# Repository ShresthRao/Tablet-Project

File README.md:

# Tablet Project
## Description
This project is a custom tablet. It contains a custom PCB and case. The PCB connects to a CM4 Lite Wireless module for processing and wireless connections. The PCB is connected to a Viekk VK1200 V2 device that is used as the digitiser, stylus and the display.

## Bill of Materials (BOM)

* Note: All prices are in USD (inclusive of GST where applicable). Production and assembly files contain additional specs where applicable.
* Note: Bom for Item 4: JLCPCB Custom Manufactured PCB is in /Production/assembly/Custom Tablet_bom_raw.csv, /Production/assembly/Custom Tablet_jlcpcb_bom.csv

### Purchased Components

| Item | Qty | Component | Price/1 Item (USD) | Link | Description |
| :---: | :---: | :--- | :---: | :--- | :--- |
| 1 | 2 | NOVA 9060100 8000mAh 3.7V Micro LiPo Battery Pack with PCB & 100mm Cable | $9.34 | [Robu.in](https://robu.in/product/nova-9060100-8000mah-3-7v-lipo-battery-pack/) | Lined in Parallel |
| 2 | 4 | Harwin R25-1001102 Hex Standoffs | $0.51 | [Element14](https://in.element14.com/harwin/r25-1001102/standoff-hex-f-f-brass-m2-5-11mm/dp/3754478) | Standoffs for CM4 module |
| 3 | 1 | Raspberry Pi Compute Module 4 | $110.16 | [Element14](https://in.element14.com/raspberry-pi/cm4104000/rpi-compute-module-4-lite-4gb/dp/3563487) | Compute module |
| 4 | 1 | JLCPCB Custom Manufactured PCB | $279.95 | [JLCPCB](https://cart.jlcpcb.com/quote?spm=jlcpcb.Public.2006&jlc_vid=TlcPUgdeEgRZAlRTTlRaVAFVFlRZV1IFRFgLAQdVRFIxVlNeQVBYVlxURlZbVDsOAxUeFF5JWAsCBBQFFU8NCAlJ) | Custom PCB Ordered through JLCPCB |
| 5 | 1 | VEIKK VK1200 V2 Drawing Tablet | $157.65 | [Amazon](https://www.amazon.in/gp/product/B08G8CKSWK/) | Acts as the Screen, Digitiser and Stylus |
| 6 | 1 | Heat Shrink Tubing Kit (328 pcs) | $1.64 | [Robu.in](https://robu.in/product/328pcs-heat-shrink-tube-heat-shrink-tube-kit/) | Protection against short circuits |
| 7 | 1 | High-Temperature Kapton Polyimide Tape (10mm × 33m) | $1.03 | [Robu.in](https://robu.in/product/10mm-33m-100ft-high-temperature-heat-resistant-polyimide-kapton-tape-hot/) | Insulation |
| 8 | 1 | Digital Multimeter (Small LCD, AC/DC) | $1.80 | [Robu.in](https://robu.in/product/digital-multimeter-small-yellow-color-lcd-ac-dc-measuring-voltage-current/) | Tool to check for battery voltage and proper functionality |
| 9 | 1 | Multimeter Test Probes | $1.25 | [Robu.in](https://robu.in/product/1-month-warranty-1260/) | Probes for multimeter |
| Total | | | $575 (Adjusted for future price changes) | | |

### On-Hand Hardware & Tools

* Storage: Micro-SD card (64GB+)
* Cables: 3x USB-C cables, 1x Short HDMI cable
* Wiring: Red and Black battery wire
* Tools & Consumables: Soldering iron, flux, solder, tweezers, superglue
* Peripherals: USB keyboard and mouse

## Specifications
### Screen:
11.6 inch
Laminated anti-glare
8,192 levels of pressure sensitivity
Resolution is 1920 × 1080 pixels (Full HD)
Color Gamut: 72% NTSC

### PCB
1 HDMI port for connection of VIEKK VK1200 V2 device.
1 SD card slot
2 USB-C ports
2 Connectors for CM4 Lite Wireless module
1 Solder pads for connection of batteries

### Stylus
2 battery-less styluses
8,192 levels of pressure
60 degrees of tilt
290 RPS of report rate
5080 LPI of resolution

### Case (total size of custom tablet)
202 mm width
378 mm length
24 mm tall

### Software
Raspberry Pi OS (64-bit) with VIEKK drivers

## Screenshots of the design:
### Schematic
#### Full Screenshot

#### Part-Wise screenshots

### PCB
#### Zoned

#### Un-Zoned

### CAD
#### Assembly

#### Bottom Case

#### Top Case

****

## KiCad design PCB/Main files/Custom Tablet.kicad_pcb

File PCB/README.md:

# PCB Files
These are the files that are used to make your own changes to the PCB.
They are files for personal use, not for production

## Main files
Base files to open in KiCad

## Custom Libraries and 3D models
Files to import into KiCad as Footrprints and Symbols for specific parts of the PCB.

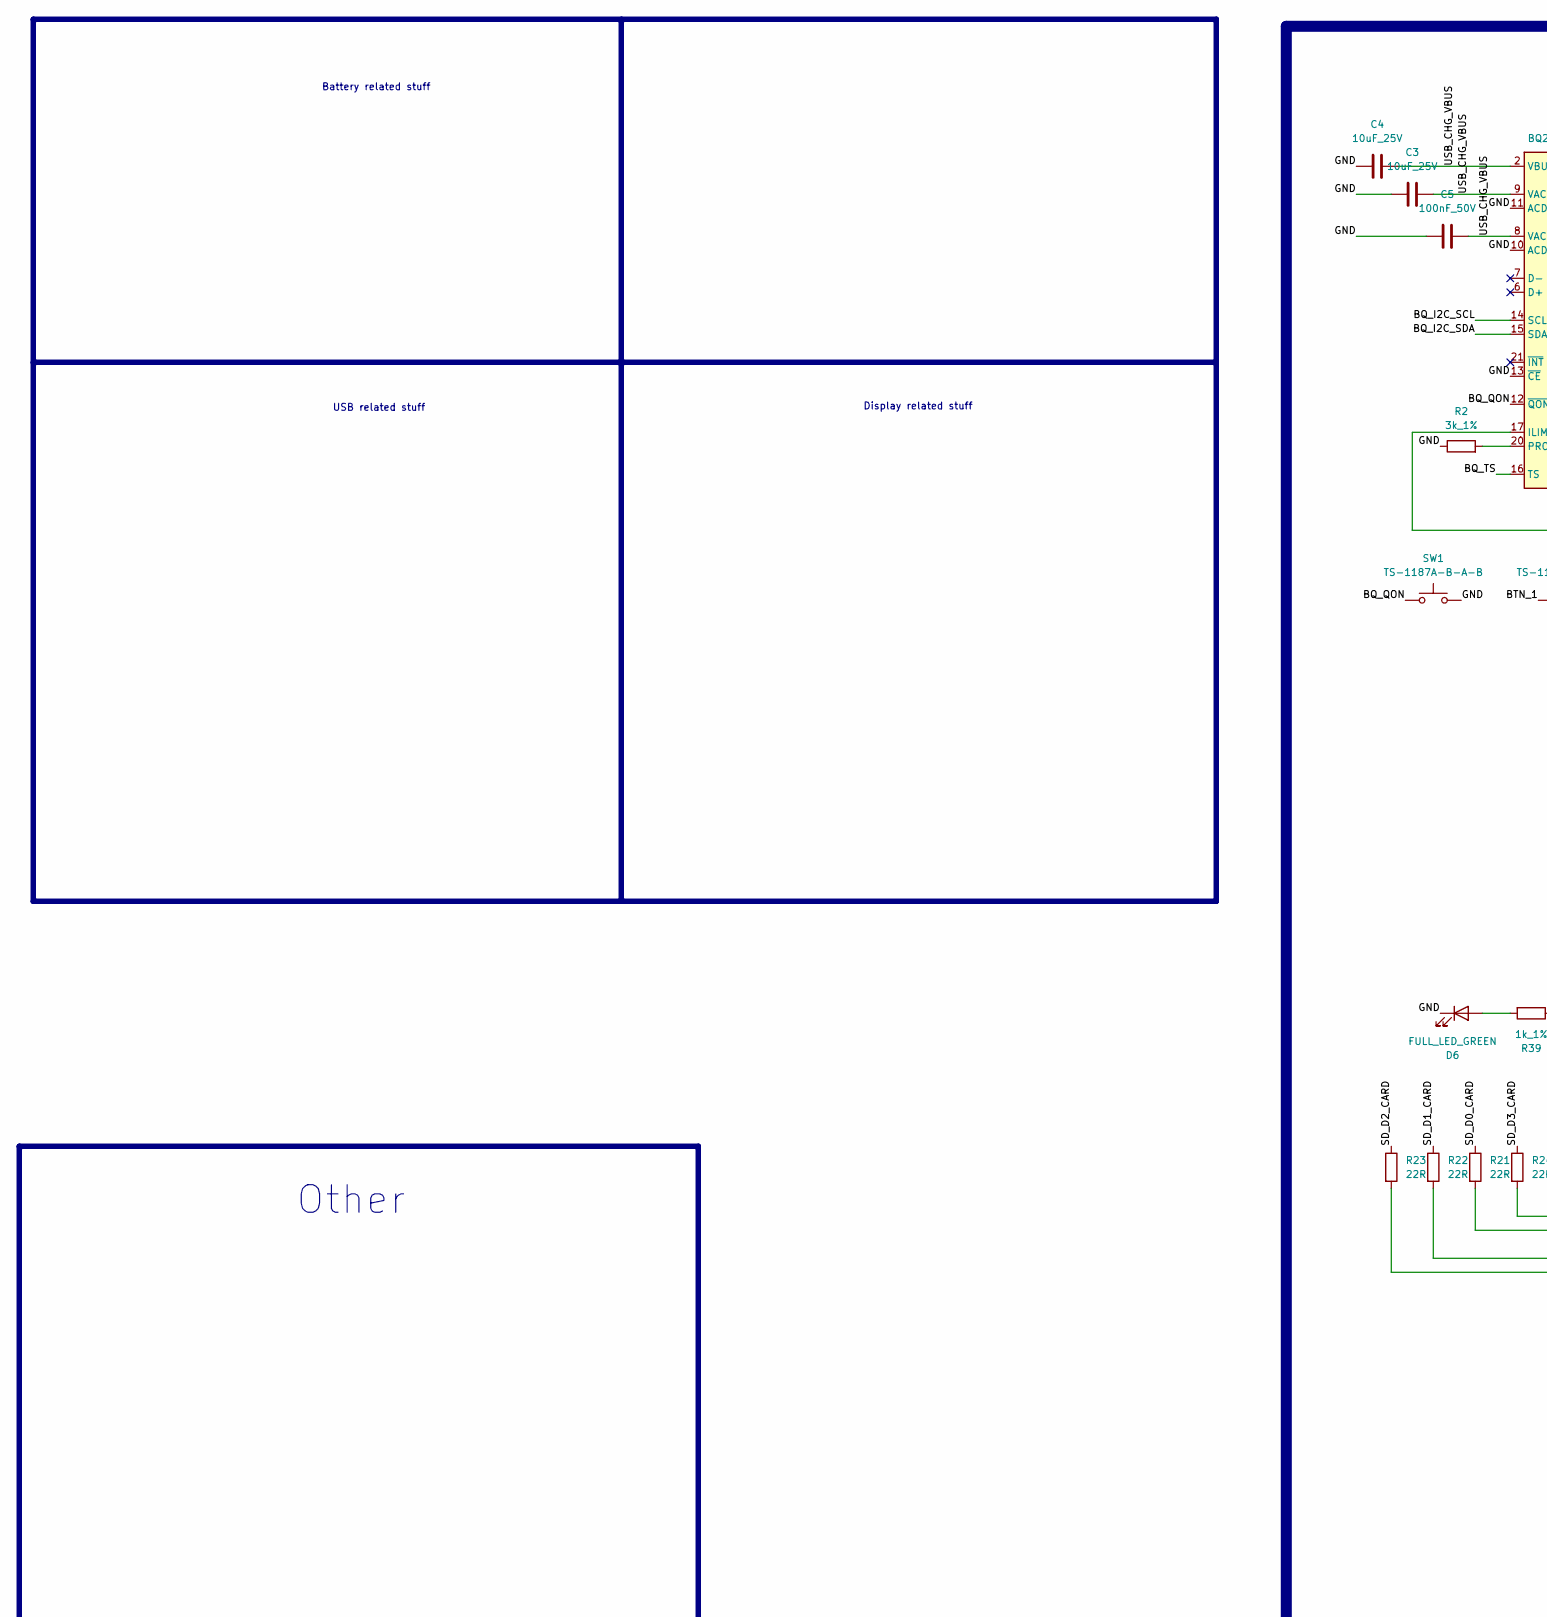
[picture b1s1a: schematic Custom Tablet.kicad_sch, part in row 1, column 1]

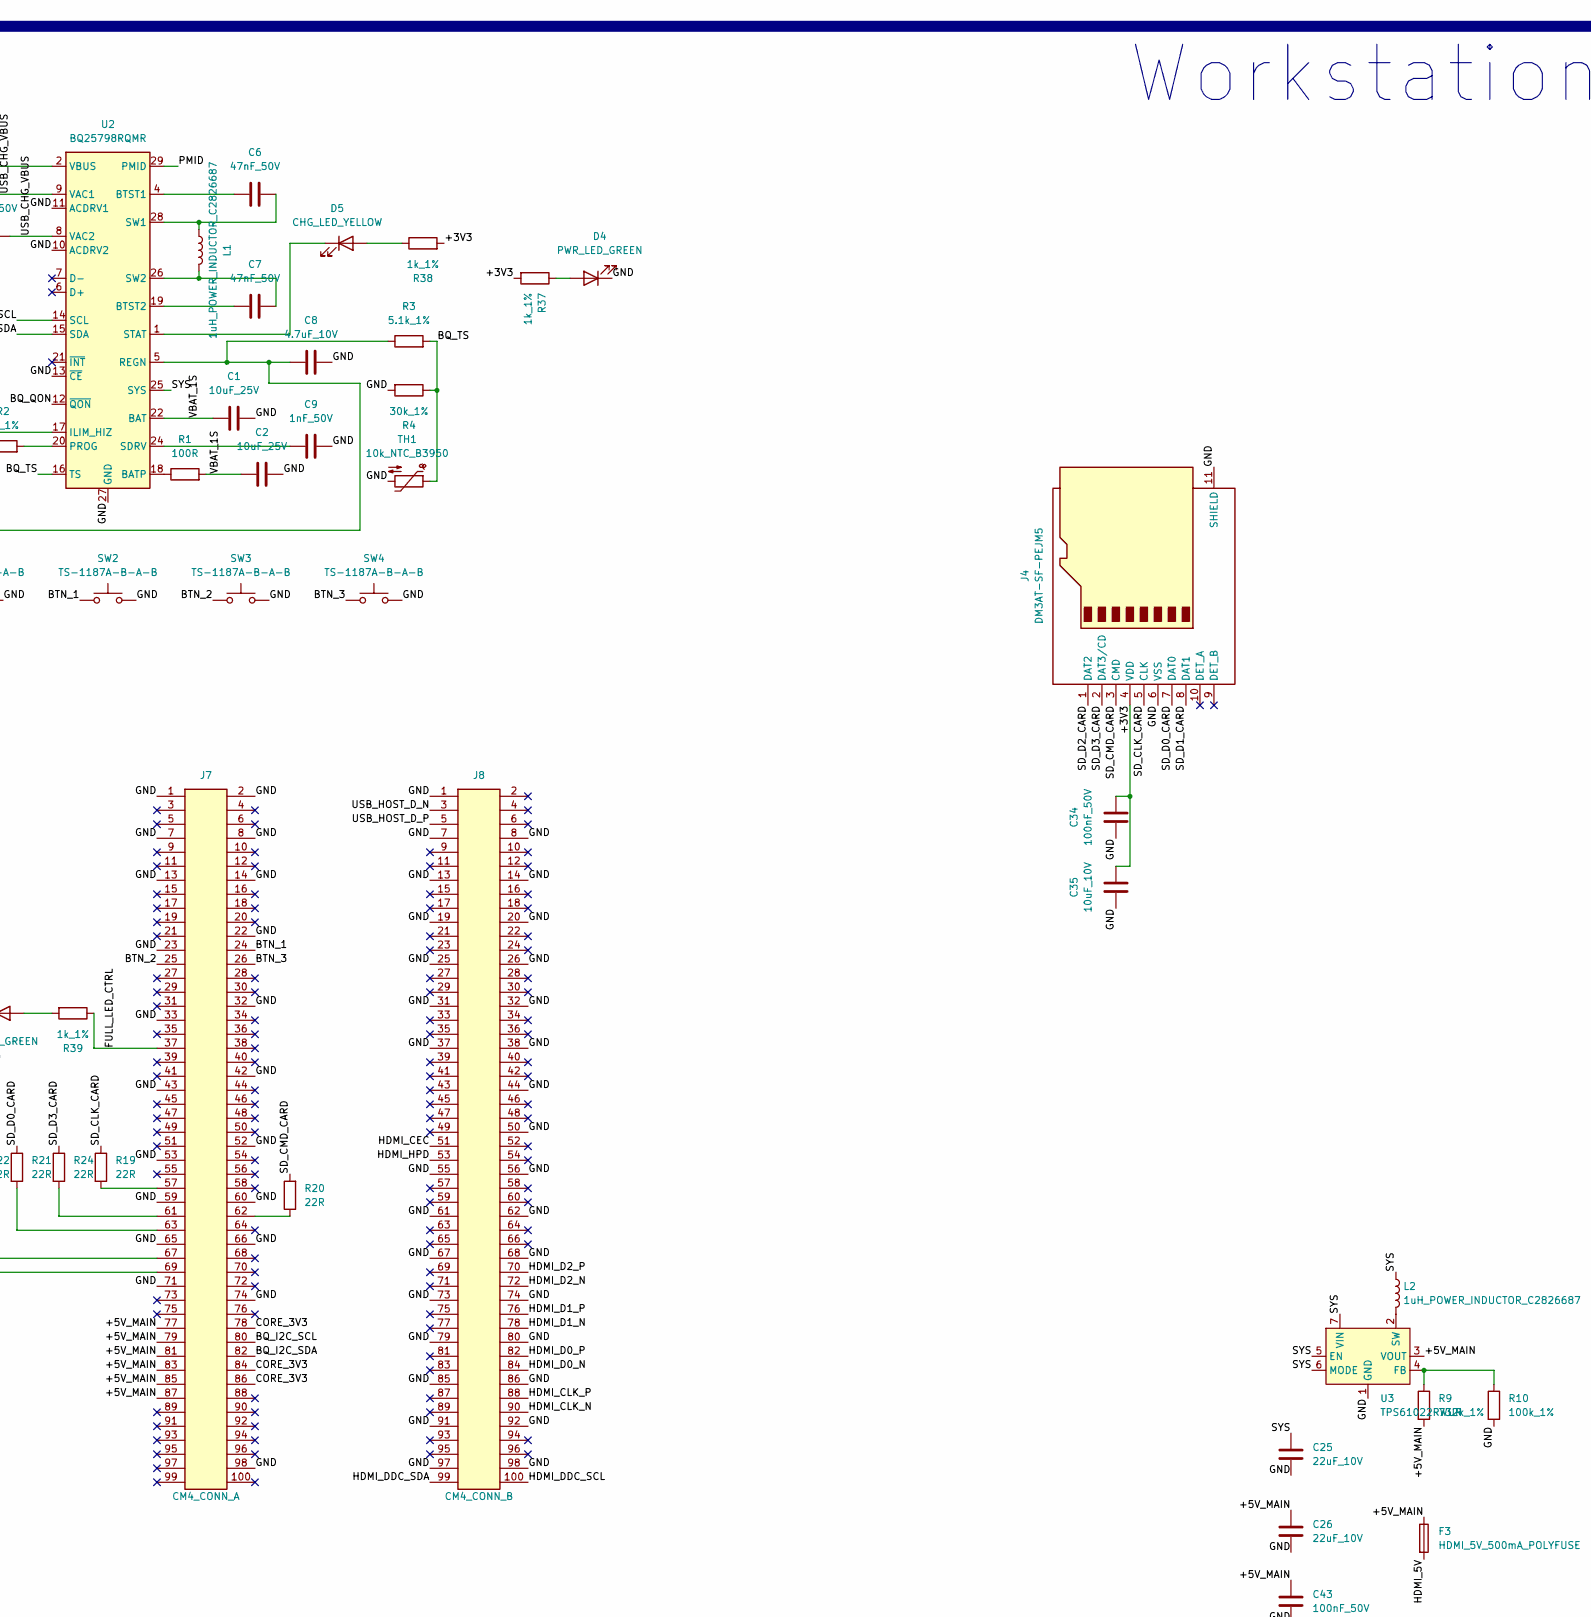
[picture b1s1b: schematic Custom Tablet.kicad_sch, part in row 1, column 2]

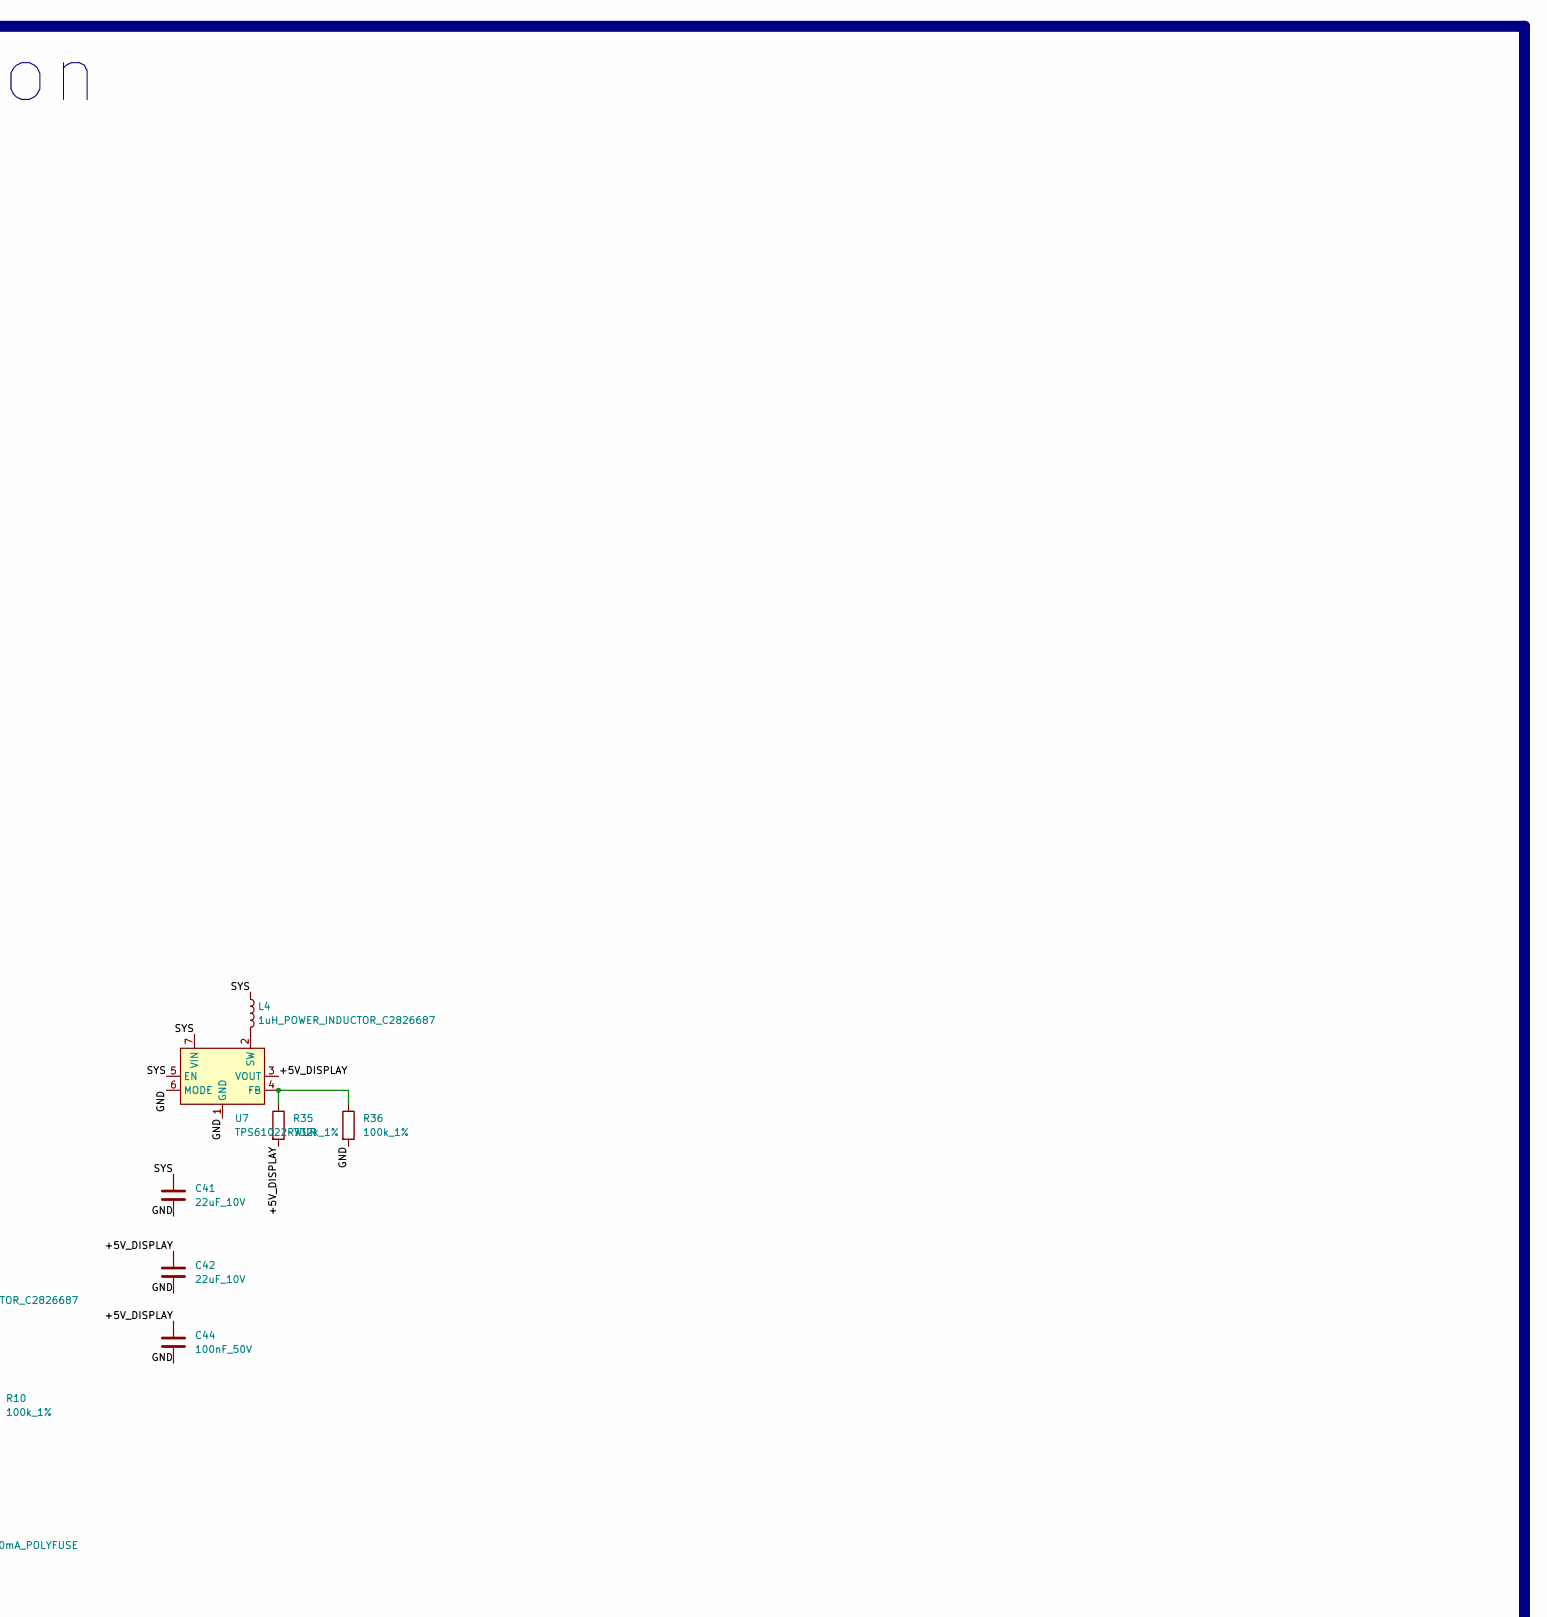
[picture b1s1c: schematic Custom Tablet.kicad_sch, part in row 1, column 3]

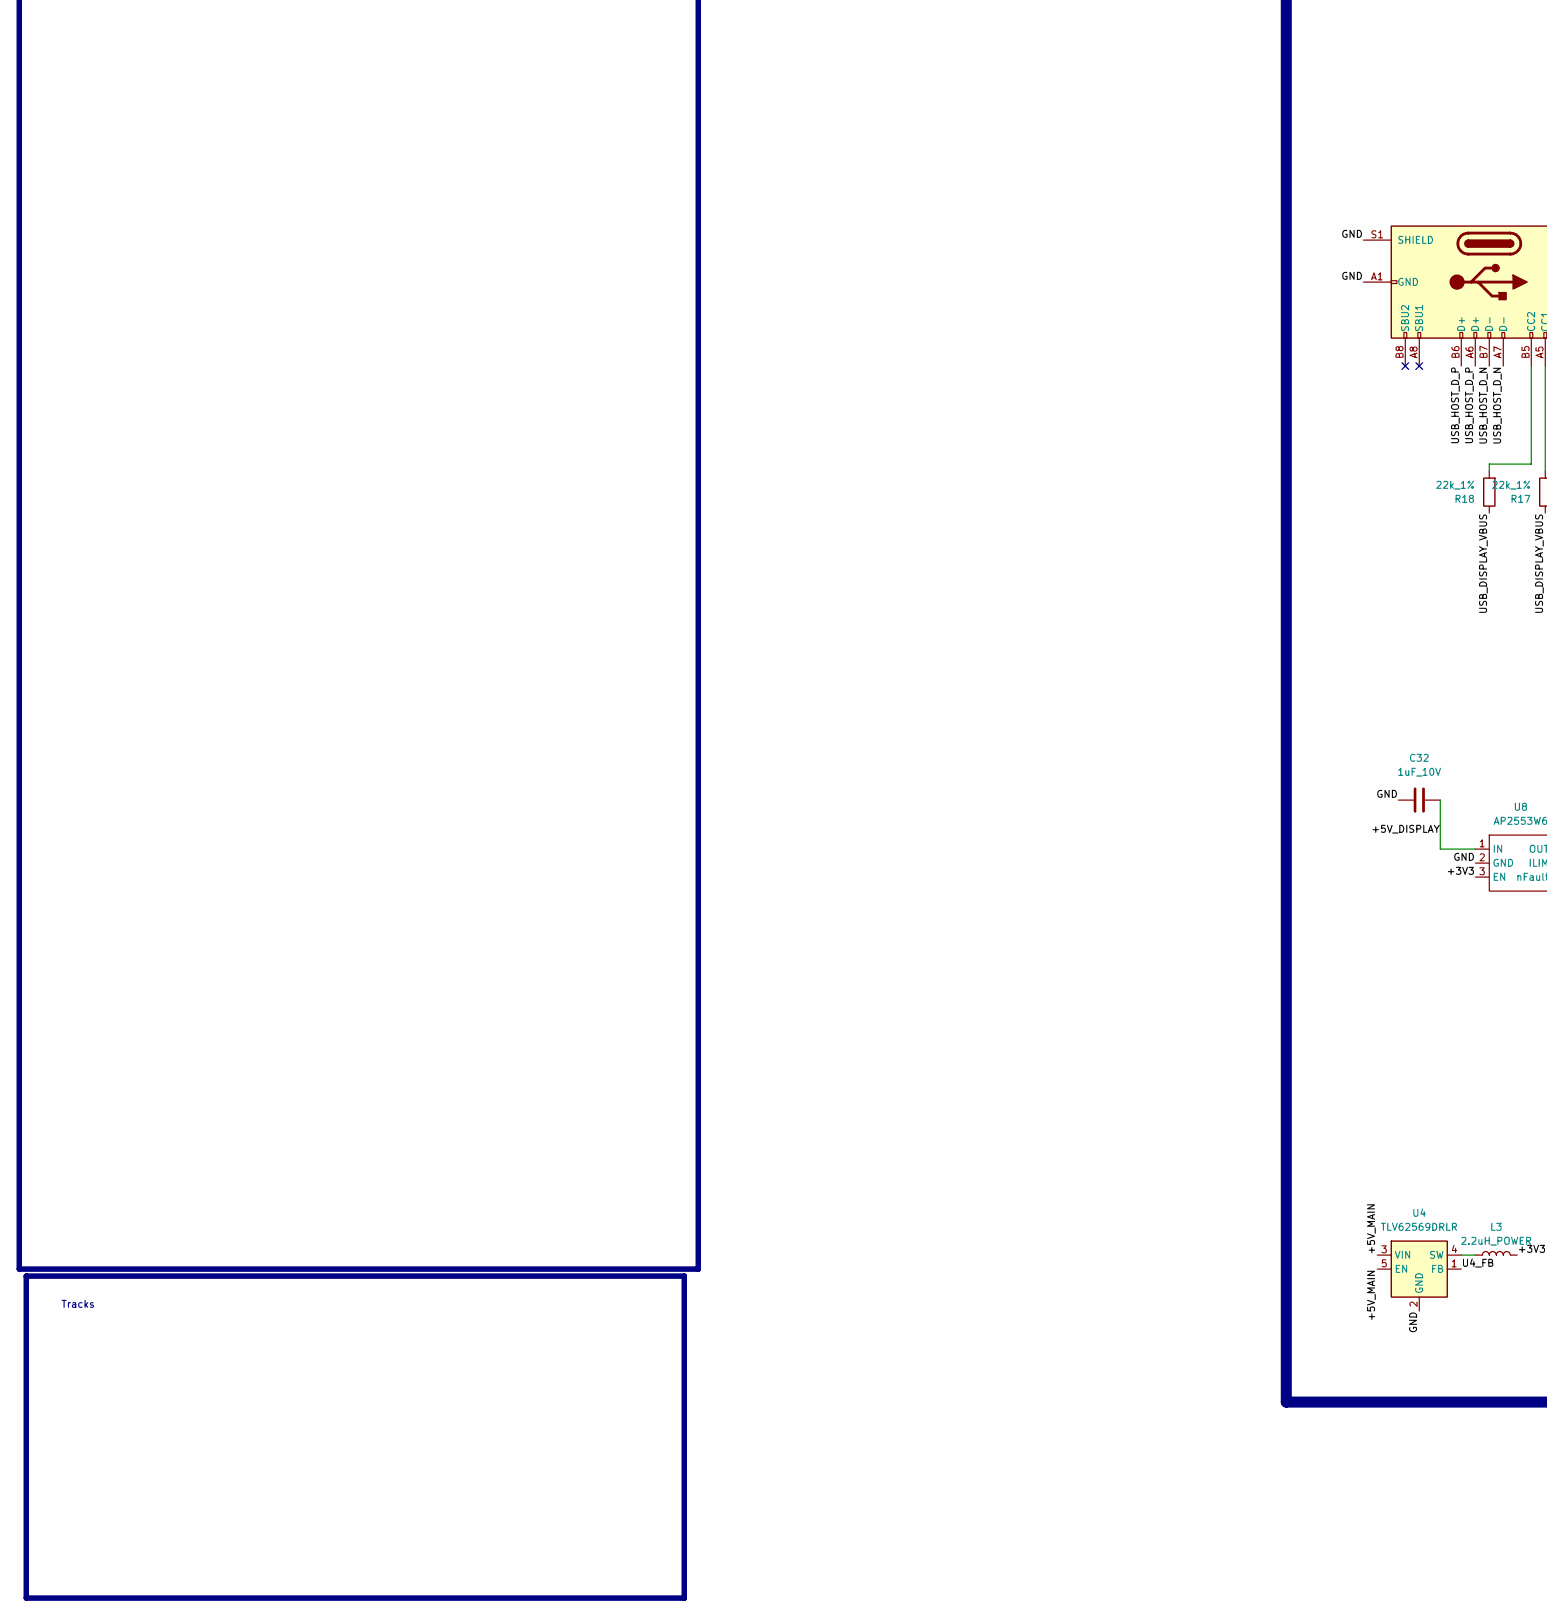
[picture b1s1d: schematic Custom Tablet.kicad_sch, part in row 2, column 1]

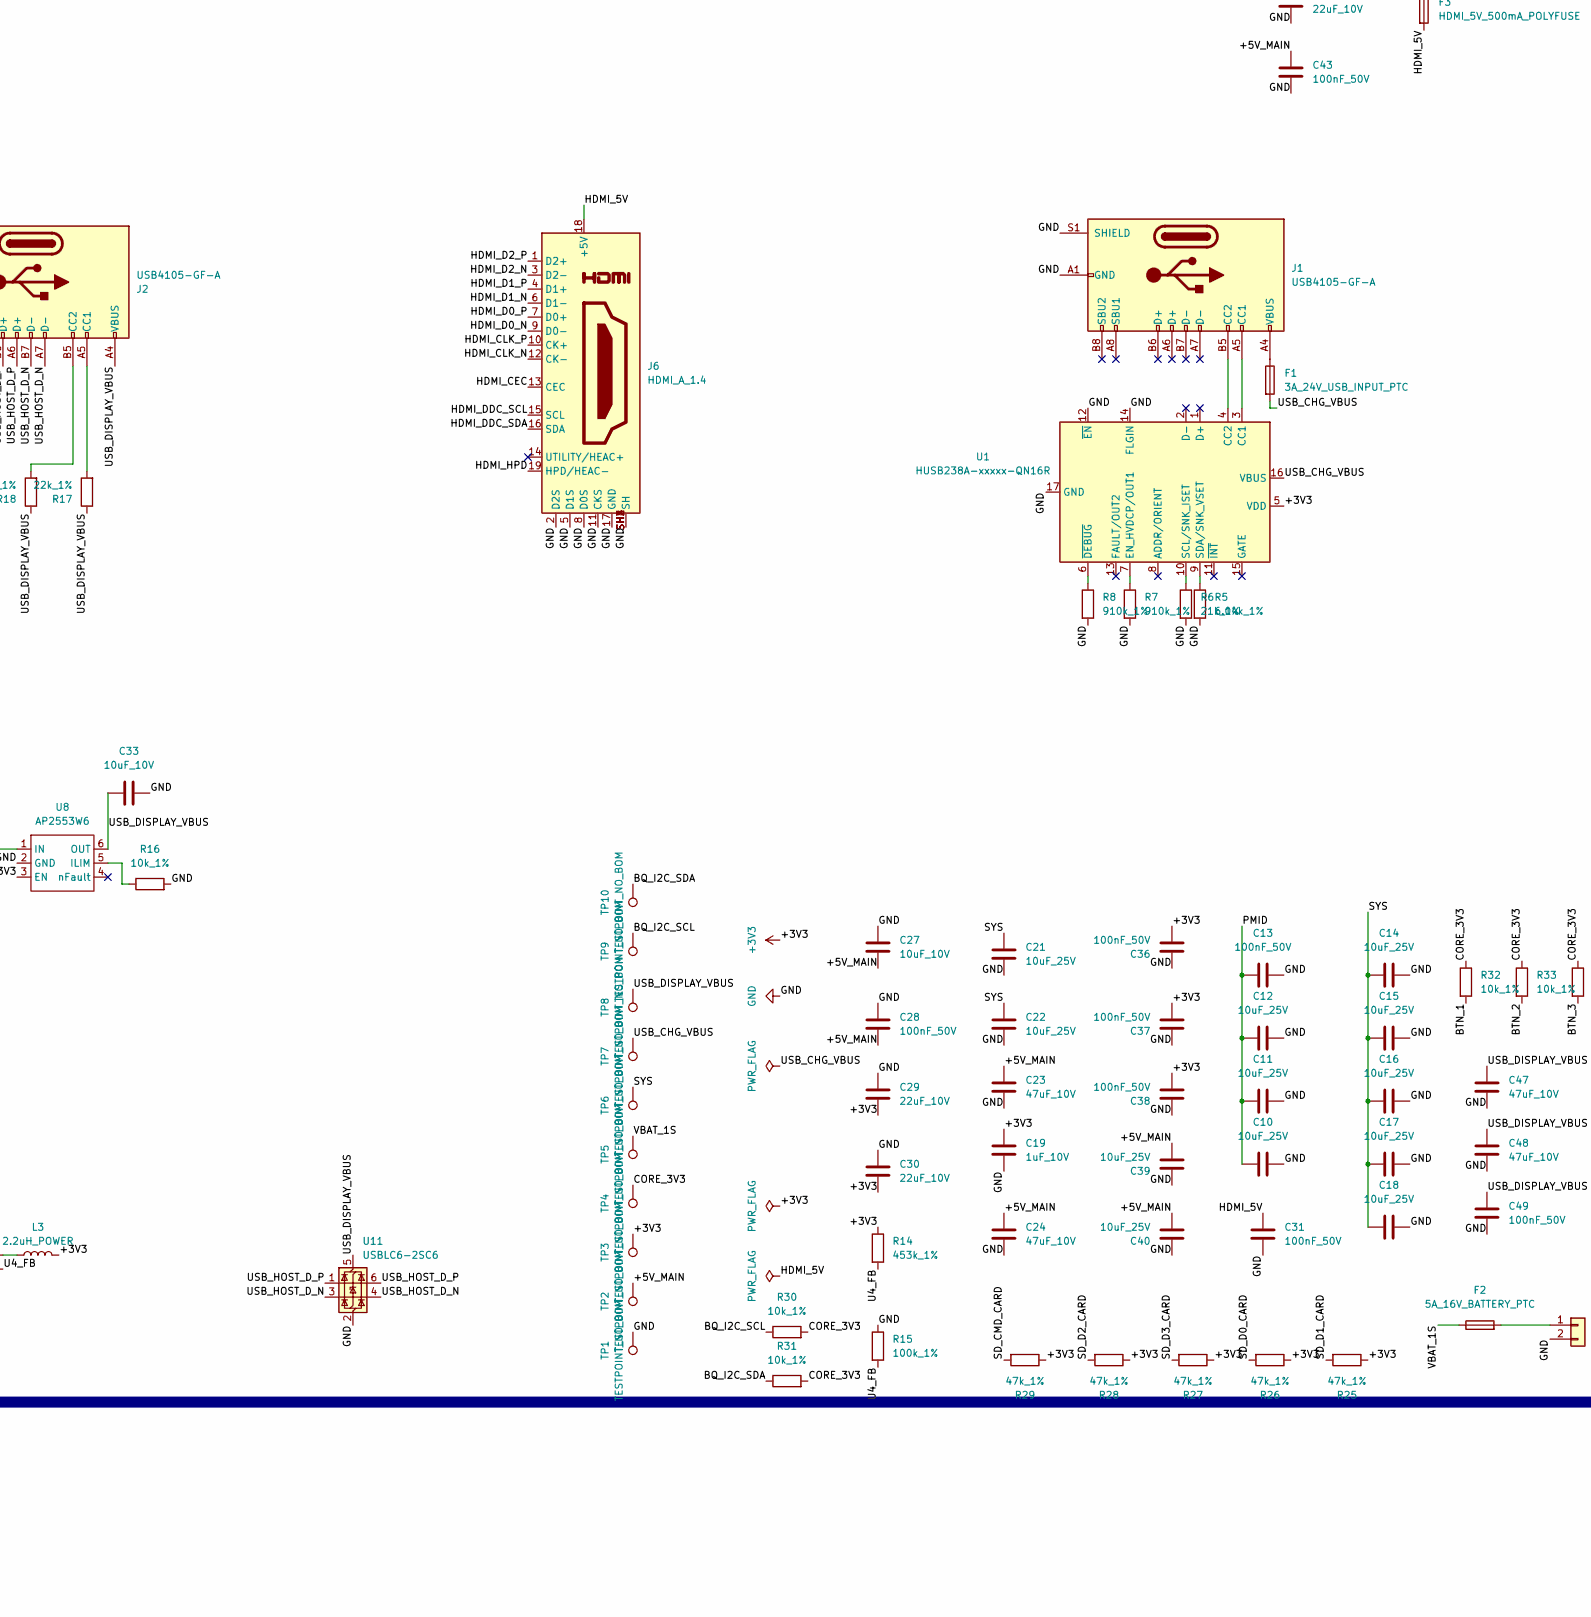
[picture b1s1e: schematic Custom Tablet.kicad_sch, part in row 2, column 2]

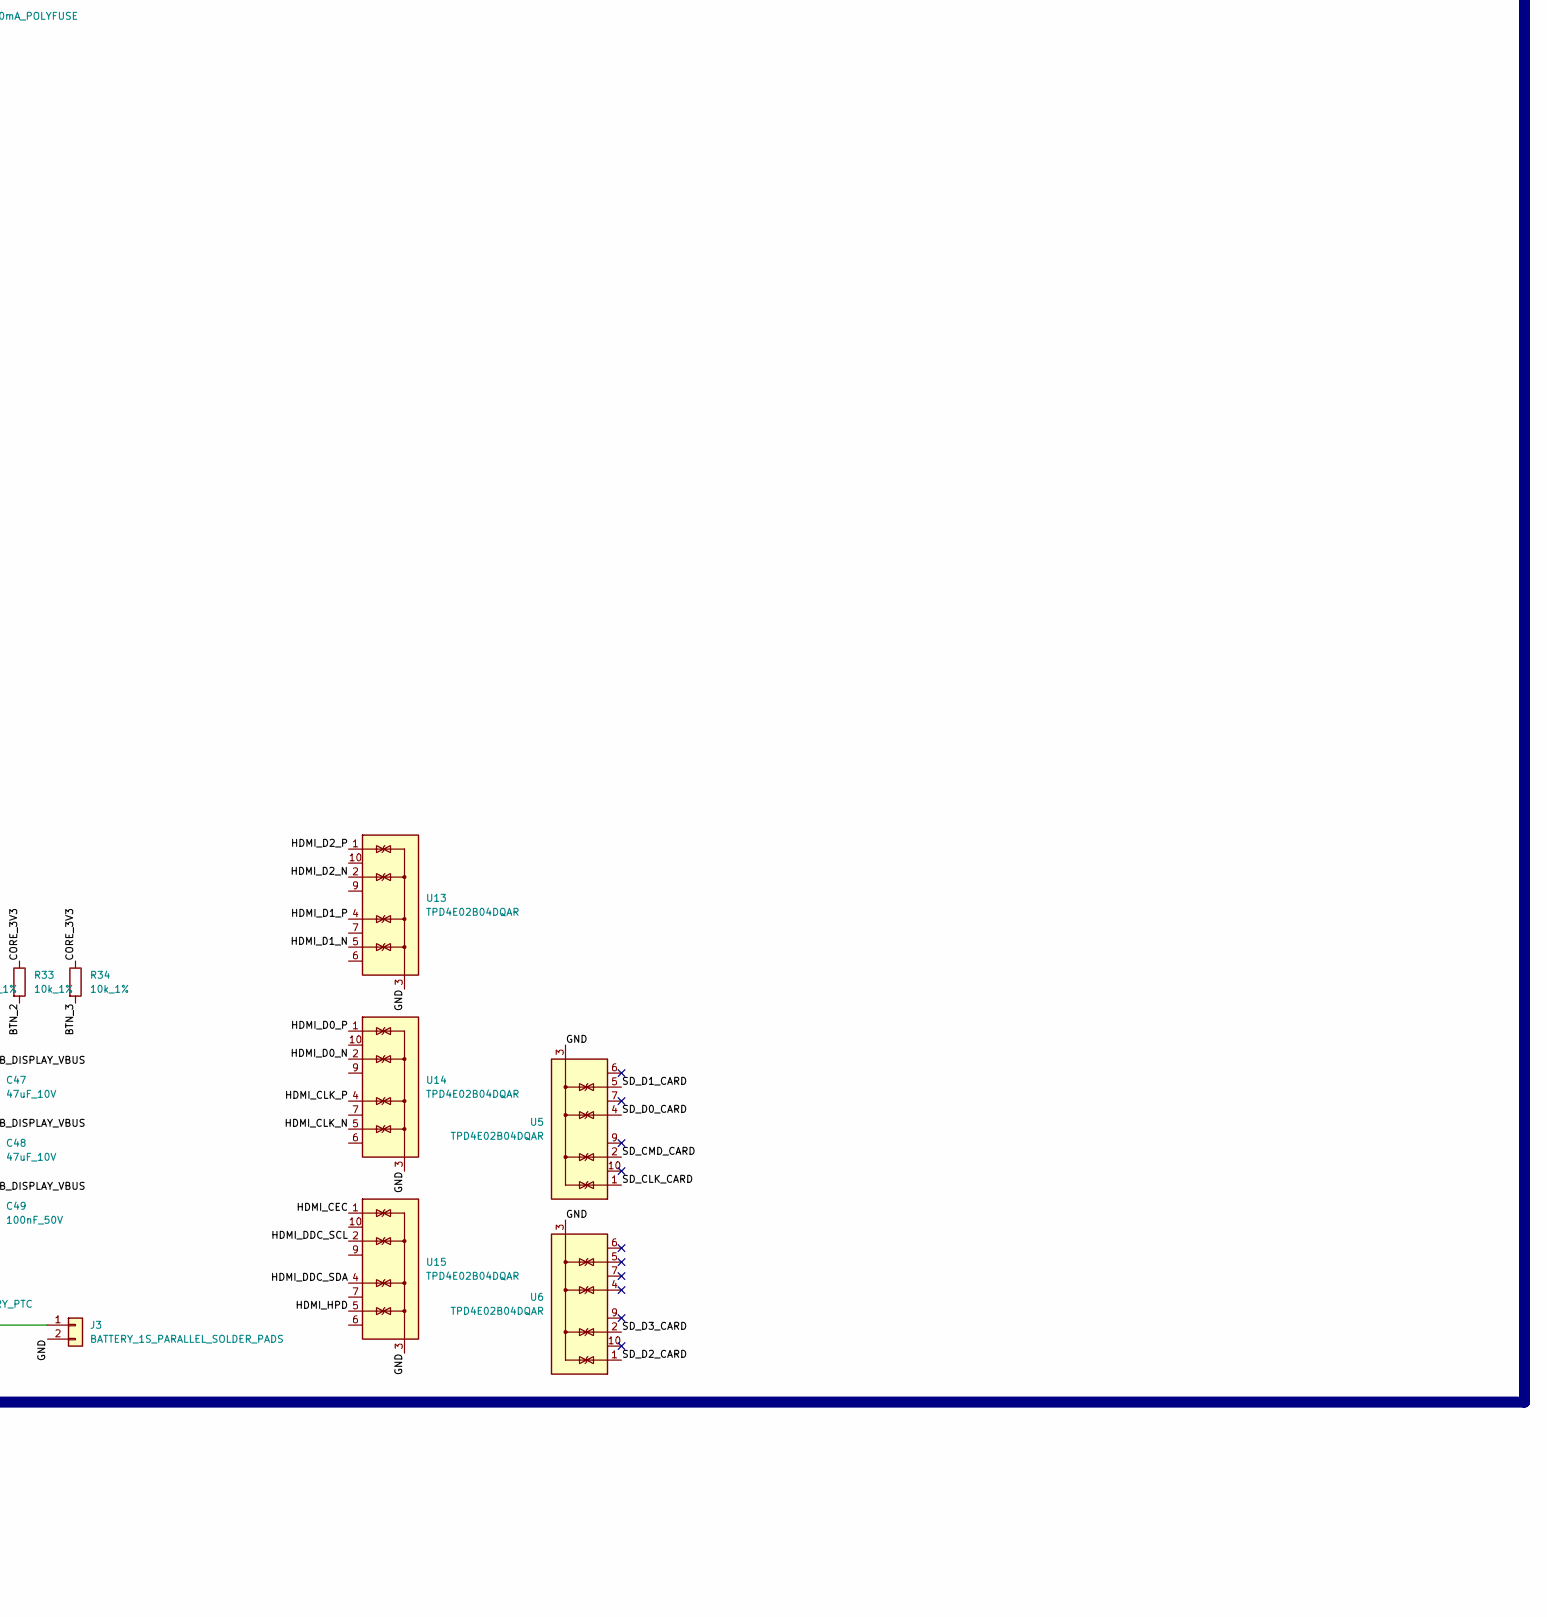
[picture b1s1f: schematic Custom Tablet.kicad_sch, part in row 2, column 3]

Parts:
C1, C2, C3, C4, C10, C11, C12, C14, C15, C16, C17, C18, C21, C22, C39, C40: 10uF_25V; C_0805_2012Metric; MPN CL21A106KAYNNNE; LCSC C15850
C5, C13, C28, C31, C34, C36, C37, C38, C43, C44, C49: 100nF_50V; C_0603_1608Metric; MPN CC0603KRX7R9BB104; LCSC C14663
C6, C7: 47nF_50V; C_0603_1608Metric; MPN CL10B473KB8NNNC; LCSC C1622
C8: 4.7uF_10V; C_0603_1608Metric; MPN CL10A475KO8NNNC; LCSC C19666
C9: 1nF_50V; C_0603_1608Metric; MPN CL10B102KB8NNNC; LCSC C1588
C19, C32: 1uF_10V; C_0603_1608Metric; MPN CL10A105KB8NNNC; LCSC C15849
C23, C24, C47, C48: 47uF_10V; C_1210_3225Metric; MPN CL32A476KOJNNNE; LCSC C2932477
C25, C26, C29, C30, C41, C42: 22uF_10V; C_0805_2012Metric; MPN CL21A226MAQNNNE; LCSC C45783
C27, C33, C35: 10uF_10V; C_0805_2012Metric; MPN CL21A106KAYNNNE; LCSC C15850
D4: PWR_LED_GREEN; LED_0603_1608Metric; MPN XL-1608UGC-06A; LCSC C7371903
D5: CHG_LED_YELLOW; LED_0603_1608Metric; MPN XL-1608UYC-06; LCSC C965802
D6: FULL_LED_GREEN; LED_0603_1608Metric; MPN XL-1608UGC-06A; LCSC C7371903
F1: 3A_24V_USB_INPUT_PTC; Fuse_2920_7451Metric; MPN BSMD2920-300-24V; LCSC C2977527
F2: 5A_16V_BATTERY_PTC; Fuse_2920_7451Metric; MPN SMD2920P500TF/16; LCSC C108585
F3: HDMI_5V_500mA_POLYFUSE; Fuse_1206_3216Metric; MPN 1206L050/15YR; LCSC C151162
J1, J2: USB4105-GF-A; USB_C_Receptacle_GCT_USB4105-xx-A_16P_TopMnt_Horizontal; MPN USB4105-GF-A; LCSC C3020560
J3: BATTERY_1S_PARALLEL_SOLDER_PADS; SolderWire-0.5sqmm_1x02_P4.6mm_D0.9mm_OD2.1mm; MPN 1S parallel battery wire solder pads; LCSC N/A
J4: DM3AT-SF-PEJM5; microSD_HC_Hirose_DM3AT-SF-PEJM5; MPN DM3AT-SF-PEJM5; LCSC C114218
J6: HDMI_A_1.4; EDAC 690-019-298-412; MPN 690-019-298-412; LCSC C5291558
J7: CM4_CONN_A; Hirose_DF40C-100DS-0.4V_2x50_P0.4mm; MPN DF40C-100DS-0.4V(51); LCSC C597931
J8: CM4_CONN_B; Hirose_DF40C-100DS-0.4V_2x50_P0.4mm; MPN DF40C-100DS-0.4V(51); LCSC C597931
L1, L2, L4: 1uH_POWER_INDUCTOR_C2826687; L_Sumida_CR75; MPN CD75-1R0M; LCSC C2826687
L3: 2.2uH_POWER; L_Bourns-SRN4018; MPN SRN4018TA-2R2M; LCSC C2044386
R1: 100R; R_0603_1608Metric; MPN 0603 100R 1%; LCSC C22775
R2: 3k_1%; R_0603_1608Metric; MPN 0603WAF3001T5E; LCSC C4211
R3: 5.1k_1%; R_0603_1608Metric; MPN 5.1k 1% 0603; LCSC C23186
R4: 30k_1%; R_0603_1608Metric; MPN 0603WAF3002T5E; LCSC C22984
R5: 6.04k_1%; R_0603_1608Metric; MPN 0603WAF6041T5E; LCSC C25977
R6: 21k_1%; R_0603_1608Metric; MPN 0603WAF2102T5E; LCSC C22956
R7, R8: 910k_1%; R_0603_1608Metric; MPN RC0603FR-07910KL; LCSC C137672
R9, R35: 732k_1%; R_0603_1608Metric; MPN 0603WAF7323T5E; LCSC C23239
R10, R15, R36: 100k_1%; R_0603_1608Metric; MPN 0603WAF1003T5E; LCSC C25803
R14: 453k_1%; R_0603_1608Metric; MPN RC0603FR-07453KL; LCSC C273765
R16, R30, R31, R32, R33, R34: 10k_1%; R_0603_1608Metric; MPN 0603WAF1002T5E; LCSC C25804
R17, R18: 22k_1%; R_0603_1608Metric; MPN 0603WAF2202T5E; LCSC C31850
R19, R20, R21, R22, R23, R24: 22R; R_0603_1608Metric; MPN 0603WAF220JT5E; LCSC C23345
R25, R26, R27, R28, R29: 47k_1%; R_0603_1608Metric; MPN 0603WAF4702T5E; LCSC C25819
R37, R38, R39: 1k_1%; R_0603_1608Metric; MPN 0603WAF1001T5E; LCSC C21190
SW1, SW2, SW3, SW4: TS-1187A-B-A-B; SW_Push_1P1T_XKB_TS-1187A; MPN TS-1187A-B-A-B; LCSC C318884
TH1: 10k_NTC_B3950; R_0603_1608Metric; MPN 10k NTC B3950; LCSC C2892547
TP1, TP2, TP3, TP4, TP5, TP6, TP7, TP8, TP9, TP10: TESTPOINT_NO_BOM; TestPoint_Pad_D1.0mm; MPN N/A; LCSC N/A
U1: HUSB238A-xxxxx-QN16R; WQFN-16-1EP_3x3mm_P0.5mm_EP1.75x1.75mm; MPN HUSB238A-BB001-QN16R; LCSC C24833806
U2: BQ25798RQMR; Texas_RQM0029A_VQFN-29_4x4mm_P0.4mm; MPN BQ25798RQMR; LCSC C2876593
U3, U7: TPS61022RWUR; Texas_RWU0007A_VQFN-7_2x2mm_P0.5mm; MPN TPS61022RWUR; LCSC C915088
U4: TLV62569DRLR; SOT-563; MPN TLV62569DRLR; LCSC C163217
U5, U6, U13, U14, U15: TPD4E02B04DQAR; USON-10_2.5x1.0mm_P0.5mm; MPN TPD4E02B04DQAR; LCSC C106794
U8: AP2553W6; SOT-23-6; MPN AP2553W6-7; LCSC C212302
U11: USBLC6-2SC6; SOT-23-6; MPN USBLC6-2SC6; LCSC C7519

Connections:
+3V3: C19.1, C29.2, C30.2, C34.2, C35.2, C36.2, C37.2, C38.2, J4.4 (VDD), L3.2, R14.1, R25.1, R26.1, R27.1, R28.1, R29.1, R37.2, R38.2, TP3.1, U1.5 (VDD), U8.3 (EN)
/+5V_DISPLAY: C32.1, C42.1, C44.1, R35.2, U7.3 (VOUT), U8.1 (IN)
/+5V_MAIN: C23.1, C24.1, C26.1, C27.2, C28.2, C39.2, C40.2, C43.1, F3.1, J7.77, J7.79, J7.81, J7.83, J7.85, J7.87, R9.2, TP2.1, U3.3 (VOUT), U4.3 (VIN), U4.5 (EN)
/BQ_I2C_SCL: J7.80, R30.1, TP9.1, U2.14 (SCL)
/BQ_I2C_SDA: J7.82, R31.1, TP10.1, U2.15 (SDA)
/BQ_QON: SW1.1, U2.12 (~QON)
/BQ_TS: R3.2, R4.1, TH1.1, U2.16 (TS)
/BTN_1: J7.24, R32.2, SW2.1
/BTN_2: J7.25, R33.2, SW3.1
/BTN_3: J7.26, R34.2, SW4.1
/CORE_3V3: J7.78, J7.84, J7.86, R30.2, R31.2, R32.1, R33.1, R34.1, TP4.1
/FULL_LED_CTRL: J7.37, R39.1
/HDMI_5V: C31.1, F3.2, J6.18 (+5V)
/HDMI_CEC: J6.13 (CEC), J8.51, U15.1 (IO1)
/HDMI_CLK_N: J6.12 (CK-), J8.90, U14.5 (IO4), U14.6 (NC)
/HDMI_CLK_P: J6.10 (CK+), J8.88, U14.4 (IO3), U14.7 (NC)
/HDMI_D0_N: J6.9 (D0-), J8.84, U14.2 (IO2), U14.9 (NC)
/HDMI_D0_P: J6.7 (D0+), J8.82, U14.1 (IO1), U14.10 (NC)
/HDMI_D1_N: J6.6 (D1-), J8.78, U13.5 (IO4)
/HDMI_D1_P: J6.4 (D1+), J8.76, U13.4 (IO3)
/HDMI_D2_N: J6.3 (D2-), J8.72, U13.2 (IO2)
/HDMI_D2_P: J6.1 (D2+), J8.70, U13.1 (IO1)
/HDMI_DDC_SCL: J6.15 (SCL), J8.100, U15.2 (IO2)
/HDMI_DDC_SDA: J6.16 (SDA), J8.99, U15.4 (IO3)
/HDMI_HPD: J6.19 (HPD/HEAC-), J8.53, U15.5 (IO4)
/PMID: C10.1, C11.1, C12.1, C13.1, U2.29 (PMID)
/SD_CLK_CARD: J4.5 (CLK), R19.1, U5.1 (IO1)
/SD_CMD_CARD: J4.3 (CMD), R20.2, R29.2, U5.2 (IO2)
/SD_D0_CARD: J4.7 (DAT0), R21.1, R26.2, U5.4 (IO3)
/SD_D1_CARD: J4.8 (DAT1), R22.1, R25.2, U5.5 (IO4)
/SD_D2_CARD: J4.1 (DAT2), R23.1, R28.2, U6.1 (IO1)
/SD_D3_CARD: J4.2 (DAT3/CD), R24.1, R27.2, U6.2 (IO2)
/U4_FB: R14.2, R15.2, U4.1 (FB)
/USB_CHG_VBUS: C3.2, C4.2, C5.2, F1.2, TP7.1, U1.16 (VBUS), U2.2 (VBUS), U2.3 (VBUS), U2.8 (VAC2), U2.9 (VAC1)
/USB_DISPLAY_VBUS: C33.1, C47.1, C48.1, C49.1, J2.A4 (VBUS), J2.A9 (VBUS), J2.B4 (VBUS), J2.B9 (VBUS), R17.1, R18.1, TP8.1, U8.6 (OUT), U11.5 (VBUS)
/USB_HOST_D_N: J2.A7 (D-), J2.B7 (D-), J8.3, U11.3 (I/O2), U11.4 (I/O2)
/USB_HOST_D_P: J2.A6 (D+), J2.B6 (D+), J8.5, U11.1 (I/O1), U11.6 (I/O1)
/VBAT_1S: C1.1, C2.1, F2.1, R1.2, TP5.1, U2.22 (BAT), U2.23 (BAT)
unnamed: D4.2 (A), R37.1
unnamed: D5.2 (A), R38.1
unnamed: D5.1 (K), U2.1 (STAT)
unnamed: D6.2 (A), R39.2
unnamed: F1.1, J1.A4 (VBUS), J1.A9 (VBUS), J1.B4 (VBUS), J1.B9 (VBUS)
unnamed: J1.A5 (CC1), U1.3 (CC1)
unnamed: J1.B5 (CC2), U1.4 (CC2)
unnamed: J2.A5 (CC1), R17.2
unnamed: J2.B5 (CC2), R18.2
unnamed: F2.2, J3.1
unnamed: J7.57, R19.2
unnamed: J7.61, R24.2
unnamed: J7.62, R20.1
unnamed: J7.63, R21.2
unnamed: J7.67, R22.2
unnamed: J7.69, R23.2
unnamed: R7.1, U1.7 (EN_HVDCP/OUT1)
unnamed: R6.1, U1.10 (SCL/SNK_ISET)
unnamed: R5.1, U1.9 (SDA/SNK_VSET)
unnamed: R8.1, U1.6 (~DEBUG)
unnamed: R1.1, U2.18 (BATP)
unnamed: C6.1, U2.4 (BTST1)
unnamed: C7.1, U2.19 (BTST2)
unnamed: C8.1, R3.1, U2.5 (REGN), U2.17 (ILIM_HIZ)
unnamed: R2.2, U2.20 (PROG)
unnamed: C9.1, U2.24 (SDRV)
unnamed: C6.2, L1.1, U2.28 (SW1)
unnamed: C7.2, L1.2, U2.26 (SW2)
unnamed: R9.1, R10.1, U3.4 (FB)
unnamed: L2.2, U3.2 (SW)
unnamed: L3.1, U4.4 (SW)
unnamed: R35.1, R36.1, U7.4 (FB)
unnamed: L4.2, U7.2 (SW)
unnamed: R16.1, U8.5 (ILIM)

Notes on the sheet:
Battery related stuff
Other
Workstation
Tracks
Display related stuff
USB related stuff

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
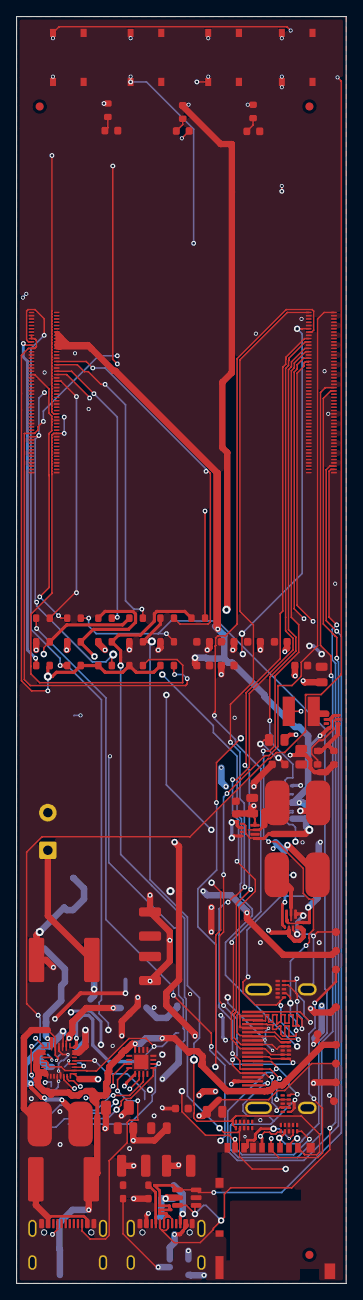
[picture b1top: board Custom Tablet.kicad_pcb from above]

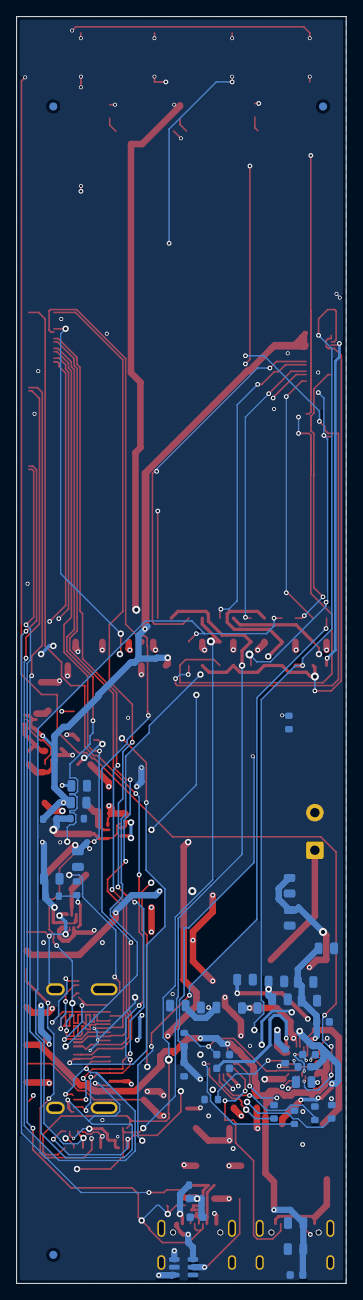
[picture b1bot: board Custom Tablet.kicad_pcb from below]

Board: 4 copper layers, 40.3 x 155.0 mm, 131 parts (43 on the bottom side), 74 nets.

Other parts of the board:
JLC_FID_BOT_1, JLC_FID_BOT_2, JLC_FID_BOT_3: JLC_GLOBAL_FIDUCIAL; Fiducial_1mm_Mask2mm
JLC_FID_TOP_1, JLC_FID_TOP_2, JLC_FID_TOP_3: JLC_GLOBAL_FIDUCIAL; Fiducial_1mm_Mask2mm
